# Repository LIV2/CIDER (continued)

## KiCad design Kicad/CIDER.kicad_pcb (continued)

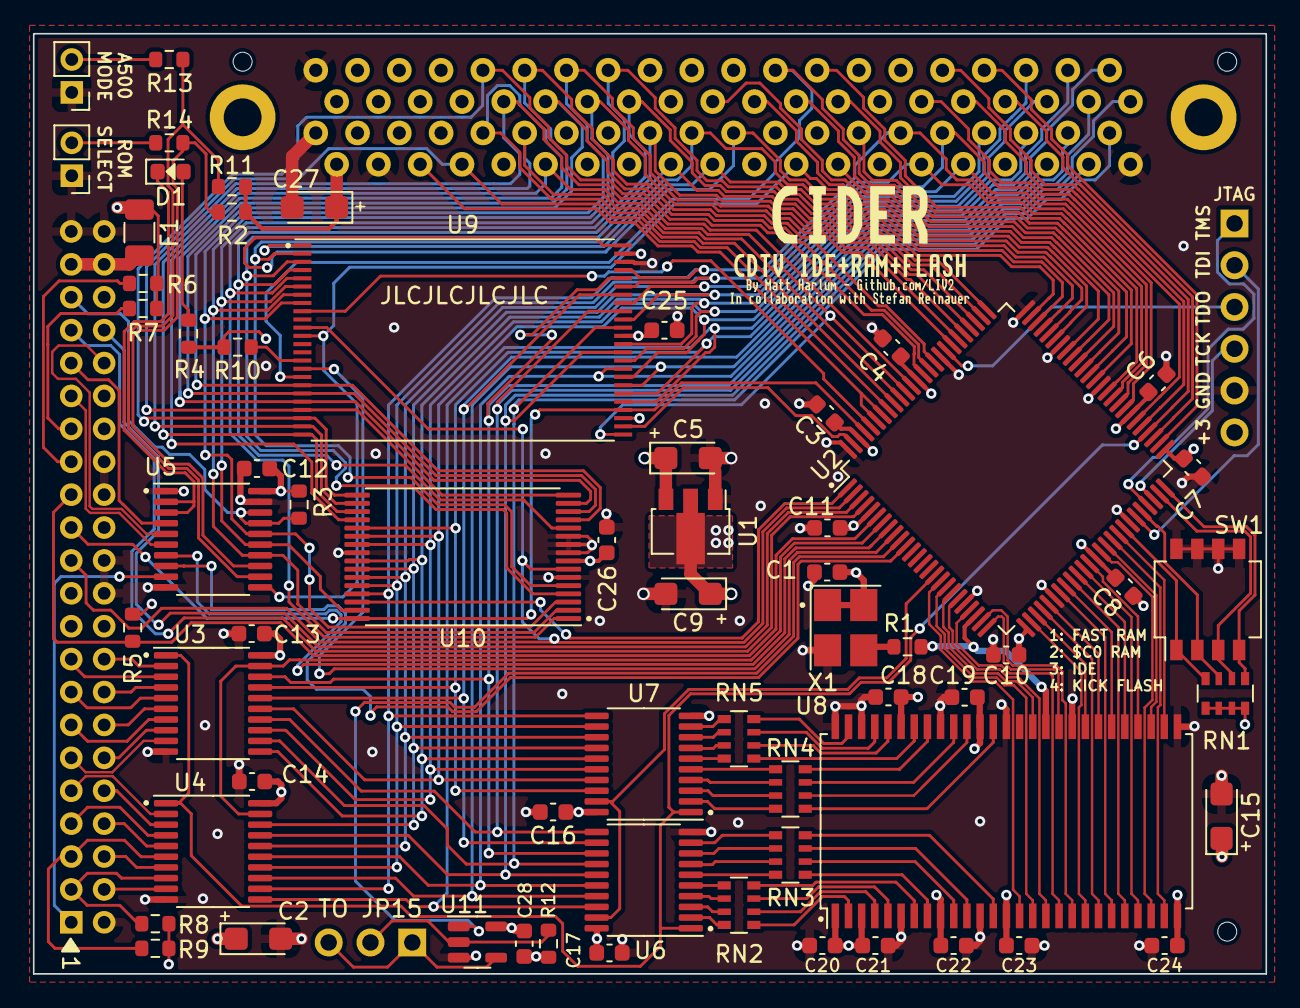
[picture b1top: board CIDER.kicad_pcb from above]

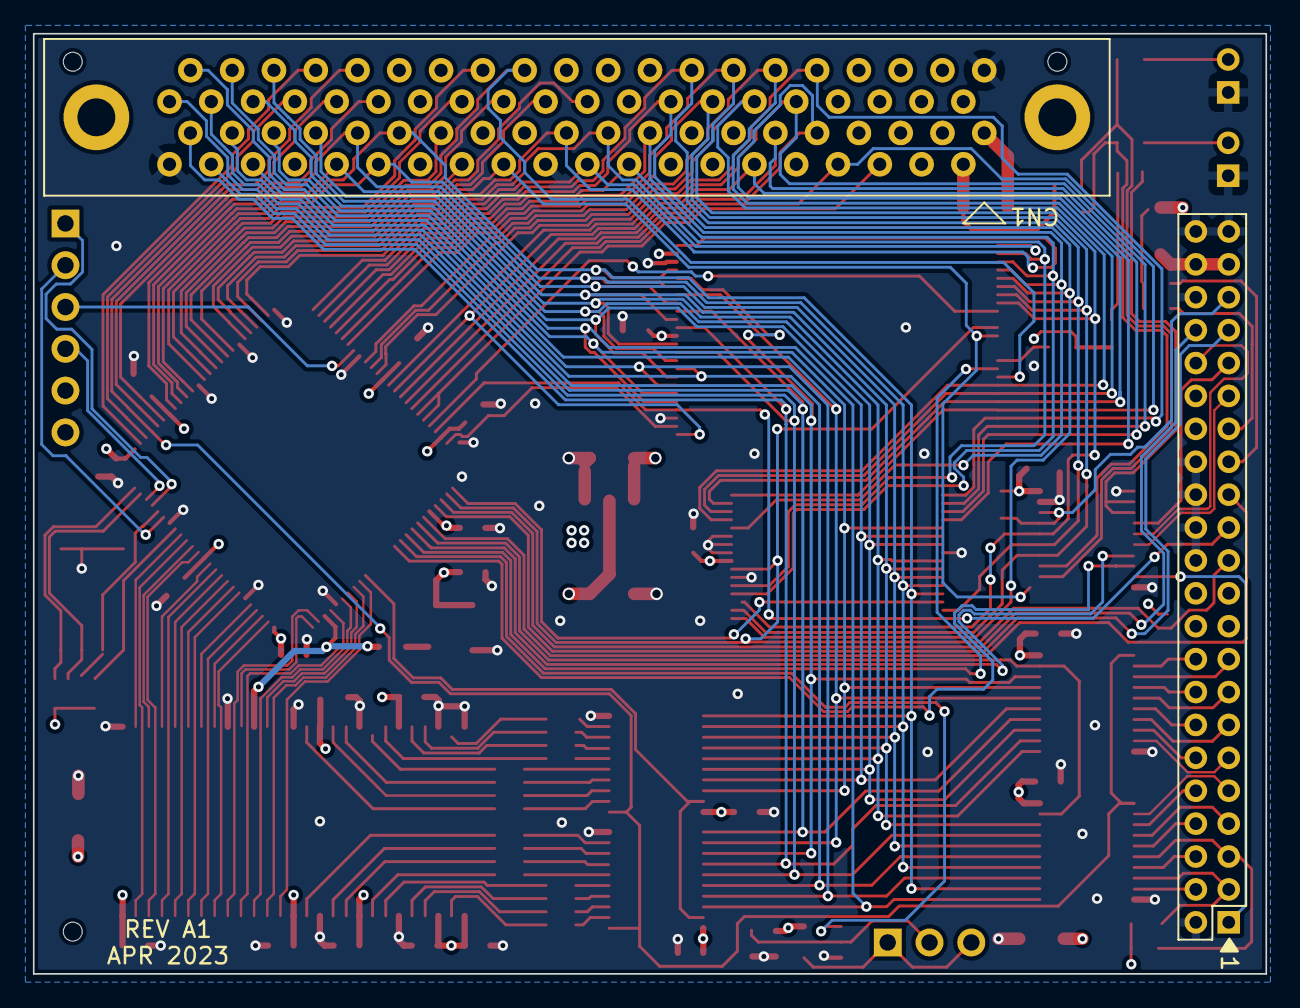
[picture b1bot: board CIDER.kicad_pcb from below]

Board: 4 copper layers, 74.9 x 57.1 mm, 72 parts (2 on the bottom side), 161 nets.

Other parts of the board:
kibuzzard-63D81BD7: G***; kibuzzard-63D81BD7
kibuzzard-63D81BF2: G***; kibuzzard-63D81BF2
kibuzzard-6443E00F: G***; kibuzzard-6443E00F
kibuzzard-6443E01A: G***; kibuzzard-6443E01A

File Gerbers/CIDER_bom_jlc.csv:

"Comment","Designator","Footprint","LCSC Part #"
"0.1u","C1,C3,C4,C6,C7,C8,C10,C11,C12,C13,C14,C16,C17,C18,C19,C20,C21,C22,C23,C24,C25,C26,C28","C_0603_1608Metric","C14663"
"10u","C9,C15","CP_EIA-3216-18_Kemet-A","C7171"
"47u","C2,C5,C27","CP_EIA-3216-18_Kemet-A","C193224"
"ACT","D1","LED_0603_1608Metric","C264450"
"Polyfuse 500mA Hold","F1","Fuse_1206_3216Metric","C151162"
"33","R1","R_0603_1608Metric","C23140"
"220","R4","R_0603_1608Metric","C22962"
"1K","R13,R14","R_0603_1608Metric","C21190"
"10K","R2,R3,R5,R6,R7,R8,R9,R10,R11,R12","R_0603_1608Metric","C25804"
"22","RN2,RN3,RN4,RN5","R_Array_Convex_4x0603","C107373"
"10K","RN1","R_Array_Convex_4x0603","C110924"
"SW_DIP_x04","SW1","SW_DIP_SPSTx04_Slide_Omron_A6H-4101_W6.15mm_P1.27mm","C397291"
"29F160","U9","TSOP-I-48_18.4x12mm_P0.5mm",""
"74HCT245","U3,U4,U5","TSSOP-20_4.4x6.5mm_P0.65mm","C6779"
"74LVC1G32","U11","SOT-23-5","C10096"
"74LVC245","U6,U7","TSSOP-20_4.4x6.5mm_P0.65mm","C7848"
"AZ1117CR-3.3","U1","SOT-89-3","C460428"
"MT48LC8M16A2P","U8","TSOP-II-54_22.2x10.16mm_P0.8mm","C62379"
"SST39SF010","U10","TSOP-I-32_11.8x8mm_P0.5mm",""
"XC95144XL-TQ100","U2","TQFP-100_14x14mm_P0.5mm","C45126"
"50MHz","X1","Oscillator_SMD_Abracon_ASE-4Pin_3.2x2.5mm_HandSoldering","C46327"

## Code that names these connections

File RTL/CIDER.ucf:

NET "ADDR<1>"  LOC = "P90"  ;
NET "ADDR<10>"  LOC = "P82"  ;
NET "ADDR<11>"  LOC = "P77"  ;
NET "ADDR<12>"  LOC = "P78"  ;
NET "ADDR<13>"  LOC = "P80"  ;
NET "ADDR<14>"  LOC = "P79"  ;
NET "ADDR<15>"  LOC = "P74"  ;
NET "ADDR<16>"  LOC = "P76"  ;
NET "ADDR<17>"  LOC = "P73"  ;
NET "ADDR<18>"  LOC = "P66"  ;
NET "ADDR<19>"  LOC = "P67"  ;
NET "ADDR<2>"  LOC = "P91"  ;
NET "ADDR<20>"  LOC = "P63"  ;
NET "ADDR<21>"  LOC = "P64"  ;
NET "ADDR<22>"  LOC = "P68"  ;
NET "ADDR<23>"  LOC = "P65"  ;
NET "ADDR<3>"  LOC = "P89"  ;
NET "ADDR<4>"  LOC = "P87"  ;
NET "ADDR<5>"  LOC = "P93"  ;
NET "ADDR<6>"  LOC = "P92"  ;
NET "ADDR<7>"  LOC = "P85"  ;
NET "ADDR<8>"  LOC = "P86"  ;
NET "ADDR<9>"  LOC = "P81"  ;
NET "AS_n"  LOC = "P53"  ;
NET "BA<0>"  LOC = "P27"  ;
NET "BA<1>"  LOC = "P29"  ;
NET "BERR_n"  LOC = "P70"  ;
NET "CAS_n"  LOC = "P20"  ;
NET "CKE"  LOC = "P25"  ;
NET "DBUS<12>"  LOC = "P59"  ;
NET "DBUS<13>"  LOC = "P58"  ;
NET "DBUS<14>"  LOC = "P61"  ;
NET "DBUS<15>"  LOC = "P60"  ;
NET "DQMH"  LOC = "P19"  ;
NET "DQML"  LOC = "P17"  ;
NET "DTACK_n"  LOC = "P56"  ;
NET "ECLK"  LOC = "P71"  ;
NET "EXTEN_n"  LOC = "P10"  ;
NET "A500_n"   LOC = "P11"  ;
NET "FLASH_A18"  LOC = "P9"  ;
NET "FLASH_A19"  LOC = "P96"  ;
NET "FLASH_BANK_SEL_n"  LOC = "P8"  ;
NET "FLASH_CE_n"  LOC = "P99"  ;
NET "FLASH_EN_n"  LOC = "P50"  ;
NET "IDE_ROMEN"  LOC = "P1"  ;
NET "IDEBUF_OE"  LOC = "P7"  ;
NET "IDECS1_n"  LOC = "P4"  ;
NET "IDECS2_n"  LOC = "P3"  ;
NET "IDEEN_n"  LOC = "P49"  ;
NET "IOR_n"  LOC = "P97"  ;
NET "IORDY"  LOC = "P6"  ;
NET "IOW_n"  LOC = "P2"  ;
NET "LDS_n"  LOC = "P55"  ;
NET "MA<0>"  LOC = "P34"  ;
NET "MA<1>"  LOC = "P36"  ;
NET "MA<10>"  LOC = "P32"  ;
NET "MA<11>"  LOC = "P28"  ;
NET "MA<2>"  LOC = "P39"  ;
NET "MA<3>"  LOC = "P41"  ;
NET "MA<4>"  LOC = "P42"  ;
NET "MA<5>"  LOC = "P40"  ;
NET "MA<6>"  LOC = "P37"  ;
NET "MA<7>"  LOC = "P35"  ;
NET "MA<8>"  LOC = "P33"  ;
NET "MA<9>"  LOC = "P30"  ;
NET "MEMCLK"  BUFG = "CLK" ;
NET "MEMCLK"  LOC = "P23"  ;
NET "MEMW_n"  LOC = "P18"  ;
NET "OVR_1_n"  LOC = "P94"  ;
NET "OVR_2_n"  LOC = "P95"  ;
NET "RAM_EN_n"  LOC = "P43"  ;
NET "RAMCS_n"  LOC = "P24"  ;
NET "RAMOE_n"  LOC = "P16"  ;
NET "RANGER_EN_n"  LOC = "P46"  ;
NET "RAS_n"  LOC = "P22"  ;
NET "RESET_n"  LOC = "P72"  ;
NET "RW"  LOC = "P54"  ;
NET "UDS_n"  LOC = "P52"  ;

NET "MEMCLK" TNM_NET = MEMCLK;
TIMESPEC TS_CLK = PERIOD "MEMCLK" 50 MHz HIGH 50%;

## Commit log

2023-01-21 Initial commit.
    Start with the HDL, need to replace gayle IDE with Apollo IDE
2023-01-22 Begin PCB design
    * Added footprint for KEL connector
    * Added symbol for CDTV Diag port
    * Initial schematic entry
2023-01-22 PCB: Add 39SF010 for IDE ROM
2023-01-22 PCB: Change IDE address line connections from A2-4 to A10-12 (Gayle vs AT-Apollo style IDE)
2023-01-23 RTL: Continue implementation * Replace Gayle IDE Emulation with AT-Apollo style IDE * Rework Autoconfig module to also config IDE & Control register devices
2023-01-23 RTL: Fixup report generation
2023-01-28 PCB: Change IDE address line connections to A9-11 (AT-Bus style)
2023-01-28 PCB: Start routing PCB
2023-01-28 PCB: Keep on routing...
2023-01-29 PCB: More routing...
2023-01-29 RTL: Assign pins
2023-01-30 RTL: Pinswaps + Implement bank selection for Flash
2023-01-30 PCB: More work...
    * Add DIP Switches for Ram/Rom/IDE config
    * Route bank select signals for Flash rom
    * Flip IDE to bottom of the board
    * Add some bulk capacitors
2023-01-30 PCB: Route Flash bank switch jumper
2023-01-30 PCB: Add 22 Ohm series resistors for SDRAM
2023-01-30 Add License
2023-01-30 Add Github release workflow
2023-01-31 RTL: Force flash to upper bank during early boot
2023-01-31 PCB: Connect Flash A18 to CPLD
2023-02-02 RTL: change product id
2023-02-02 Check-in cflash util
2023-02-03 CFLASH: Correct behavior for 1MB ROMs
2023-02-03 RTL: Fix autoconfig
    The CDTV's diag port connects config_in/out to gnd making them useless.
    Wait until we see the DMAC get assigned it's address instead...
    While we're at it make the ram disable switch work
2023-02-03 PCB: Remove useless cfgin connection
2023-02-03 PCB: Fixups
    * Tweak KEL connector hole sizes
    * Fixup MT48LC8M16A2P - Had copied this from the 16M16 part and forgot to make A12 an NC
2023-02-04 CFLASH: couple of fixups
2023-02-04 Software: check-in AddRam util
2023-02-05 PCB: Connect another CPLD pin to OVR_n
    This should give more drive strength to make sure we can drive it low nice and fast
2023-02-05 RTL: Tweak OVR
    * Optimize OVR equations to make sure it is asserted as fast as possible, use less pterms
    * Drive OVR with 2 pins to give stronger drive
2023-02-05 RTL: Add timing report
2023-02-06 RTL: Fixup ctrl_access equation
2023-02-06 RTL: Add Timespec for MEMCLK
2023-02-07 PCB: Connect NC's of 39SF010 to GND
    This will allow people to substitute 39SF020/040 if the 010 ever becomes unobtanium
2023-02-07 Update PCB Render
2023-02-08 Add ground pours
    Apparently JLCPCB are now incapable of producing 4-layer PCBs with less than 30% copper on outer layers...
2023-02-09 PCB: Fix drill/component grid & U10 missing from bom
2023-02-19 cflash: fixup a bunch of mistakes & add IDE rom verify
2023-02-19 RTL: Fixups
    * Expansion ignores rom vector if it is 0, set the offset to 8
    * Fixup IDE ROM - needs to be available for full 64K range
    * Change to BSC/AT-Bus Manuf/Prod id for IDE during testing
    * Fixup autoconfig goofs
    * IDE ROM goes away after first write to IDE space
2023-02-19 cflash: Slots
    Describe top/bottom half as slots rather than banks to make usage more obvious
2023-02-19 RTL: Latch maprom enable at reset, disable autoboot rom flag when IDE disabled
2023-02-19 CFLASH: make sure to erase the right bank...
2023-02-19 RTL: Latch ranger_enable on reset
2023-02-20 Addram: fix merge behaviour
    Previously cd_BoardAddr pointed to the FastRAM board but this was changed to be the Control register
    This meant that it was looking for a memory region at the control register base
    Instead just look through the MemList to find a bordering Fast RAM chunk
2023-02-20 Bootrom: Add a kickstart module to enable A0 Bonus RAM at boot
2023-02-21 GH Actions: Build software & attach to release
2023-02-21 GH Actions: Generate kicad outputs
2023-02-21 GH Actions: Package software inside LHA & ADF
2023-02-23 Add IDE boot rom
2023-02-23 Add license to software
2023-02-23 Add READMEs for Software
2023-02-23 CFLASH: fixup usage text
2023-02-23 Fixup cflash readme
2023-02-24 iderom: rework as a chainloader module
    This way I can load a driver that uses RTF_AUTOINIT and then call mounter afterwards to add the boot entries
2023-02-28 Move Software to it's own repo
2023-03-01 GH Actions: remove steps involving software
2023-04-17 Fixup IDECS logic
2023-04-17 Control: Add flash_bank
    This will allow the cflash util to check which bank was selected at boot, so the other can be programmed
2023-04-17 Disable control flash_bank - it was not working
2023-04-17 Re-add flash_bank status in control reg
    Managed to make it fit properly this time...
2023-04-23 Fixup readme
2023-04-23 Make IDE space 128K which will allow programming flash when IDE enabled
2023-04-23 fixup 128K IDE space change
2023-04-23 Control reg: Set flash_enabled to false if mapram enabled
2023-04-23 Add mapram function
2023-04-24 Add acknowledgement to README
2023-04-25 Streamline autoconfig a bit
2023-04-25 Proto_B: Add A500 mode switch
2023-04-25 Proto_B: Add A500 mode jumper, add SMD Act LED
2023-04-25 Rev_A: Proto_B is now Rev A
    Also adds a 3D model for the KEL Connector (Thanks Eriond!)
2023-04-25 Proto B
    Add connection to CDTV JP15 to disable extended rom decode when Flash ROM active
2023-04-25 Add EXTEN_n JP15 control signal
2023-04-25 Rev_A: Generate outputs
2023-04-25 Fixup some of the JLC part numbers
2023-04-27 RTL: A500 mode disables external extended rom too
2023-04-27 add Rev_A jed...
2023-04-27 add ifndefs for Proto_A builds
2023-04-30 Rev_A1: Add pull-down resistor for U11 input, add tooling holes
2023-05-11 Rev_A: Fixup JLC Part # for Volt reg
2023-05-11 Rev_A1: Fixup JLC Part # for Volt reg
2023-05-13 Rev_A1: Invert polarity of A500 and FLASH_BANK_SEL inputs
2023-05-13 Rev-A1: Buffer A500/Bank Sel switches
    Added inline resistors to these two and buffer them via U5
    In Proto A it was found that operating the switches would cause latch-up and destroy the CPLD
2023-05-13 Rev-A1: move switch headers to top of the board and update render
2023-05-16 Fixup RAM product ID
    Was supposed to be Decimal not Hex
2023-06-09 Remove Software submodule
2023-06-12 Switch to OAHR allocated Autoconfig IDs
2023-08-10 Firmware fixes
    * IDE IOR/IOW change timing to fix IDE corruption issues
    * DTACK timing fixup, SDRAM was unnecessarily holding off DTACK
2023-08-18 RTL: FIX - Remove AS_n from OVR equation
    Assert OVR as soon as we have an address match
    If OVR comes too late then Gary will miss it and BonusRam/Flash
    programming window will conflict with CIAs
2023-08-26 Add Bill of materials with Mouser links
2023-08-26 Add photos
2024-02-09 Fixup github actions
